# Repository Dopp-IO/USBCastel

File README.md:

# USBCastel
Tiny 4-port castellated USB hub.

Part	Value	  Package  
C1	  8pF	    C0402  
C2	  8pF	    C0402  
C3	  10uF	  C0402  
C4	  10uF	  C0402  
C5	  10uF	  C0402  
C6	  0.1uF	  C0402  
IC1	  FE1.1S	SOP64P600X175-28N  
R1	  2.7K	  R0402  
X1	  12MHz	  ABM10

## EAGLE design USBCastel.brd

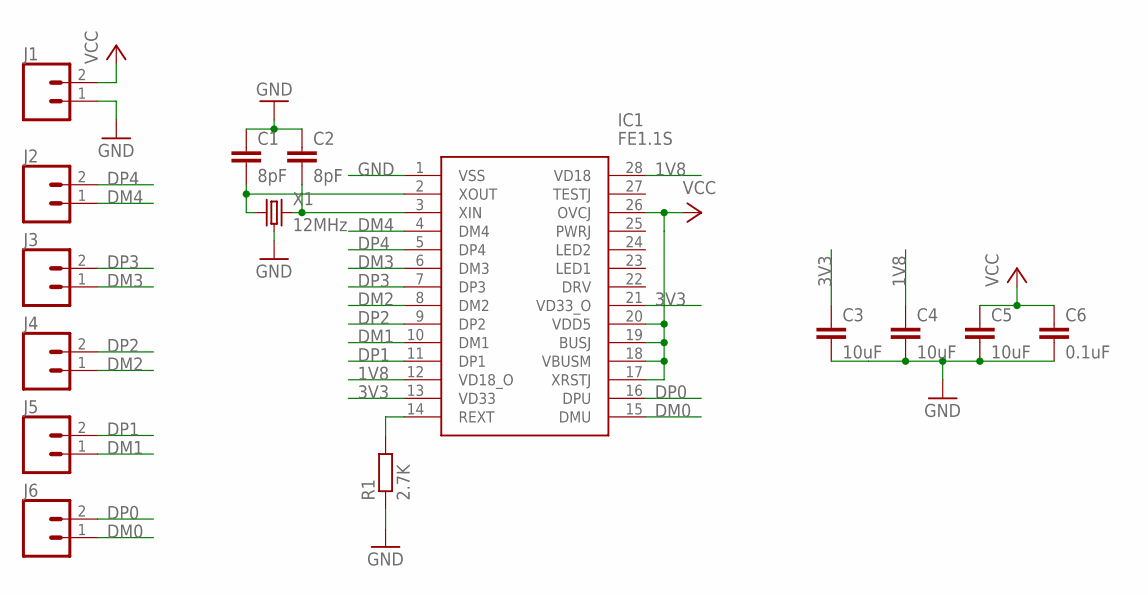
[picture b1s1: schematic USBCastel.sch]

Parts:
C1, C2: 8pF; C0402
C3, C4, C5: 10uF; C0402
C6: 0.1uF; C0402
IC1: FE1.1S; SOP64P600X175-28N
J1, J2, J3, J4, J5, J6: CONN_021X02_NO_SILK; 1X02_NO_SILK
R1: 2.7K; R0402
X1: 12MHz; ABM10

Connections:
1V8: C4.1, IC1.12 (VD18_O), IC1.28 (VD18)
3V3: C3.1, IC1.13 (VD33), IC1.21 (VD33_O)
DM0: IC1.15 (DMU), J6.1
DM1: IC1.10 (DM1), J5.1
DM2: IC1.8 (DM2), J4.1
DM3: IC1.6 (DM3), J3.1
DM4: IC1.4 (DM4), J2.1
DP0: IC1.16 (DPU), J6.2
DP1: IC1.11 (DP1), J5.2
DP2: IC1.9 (DP2), J4.2
DP3: IC1.7 (DP3), J3.2
DP4: IC1.5 (DP4), J2.2
GND: C1.1, C2.1, C3.2, C4.2, C5.2, C6.2, IC1.1 (VSS), J1.1, R1.1, X1.2 (3), X1.4 (3)
unnamed: C2.2, IC1.3 (XIN), X1.3 (2)
unnamed: C1.2, IC1.2 (XOUT), X1.1
unnamed: IC1.14 (REXT), R1.2
VCC: C5.1, C6.1, IC1.17 (XRSTJ), IC1.18 (VBUSM), IC1.19 (BUSJ), IC1.20 (VDD5), IC1.26 (OVCJ), J1.2

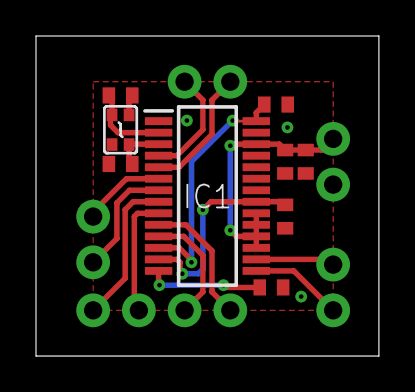
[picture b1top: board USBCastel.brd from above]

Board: 2 copper layers, 19.1 x 17.8 mm, 15 parts (0 on the bottom side), 17 nets.

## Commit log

2018-08-10 Added eagle and gerber files
2018-08-10 Updated with BOM
2018-08-10 Updated tabs
2018-08-10 Added line breaks
2018-08-10 Fixed line breaks
2018-08-10 Bottom silkscreen
2018-08-11 Added schematic PDF
2018-08-19 Fixed bottom silkscreen

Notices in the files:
parts and their libraries:
SparkFun-Connectors: Licensing: Creative Commons ShareAlike 4.0 International - https://creativecommons.org/licenses/by-sa/4.0
